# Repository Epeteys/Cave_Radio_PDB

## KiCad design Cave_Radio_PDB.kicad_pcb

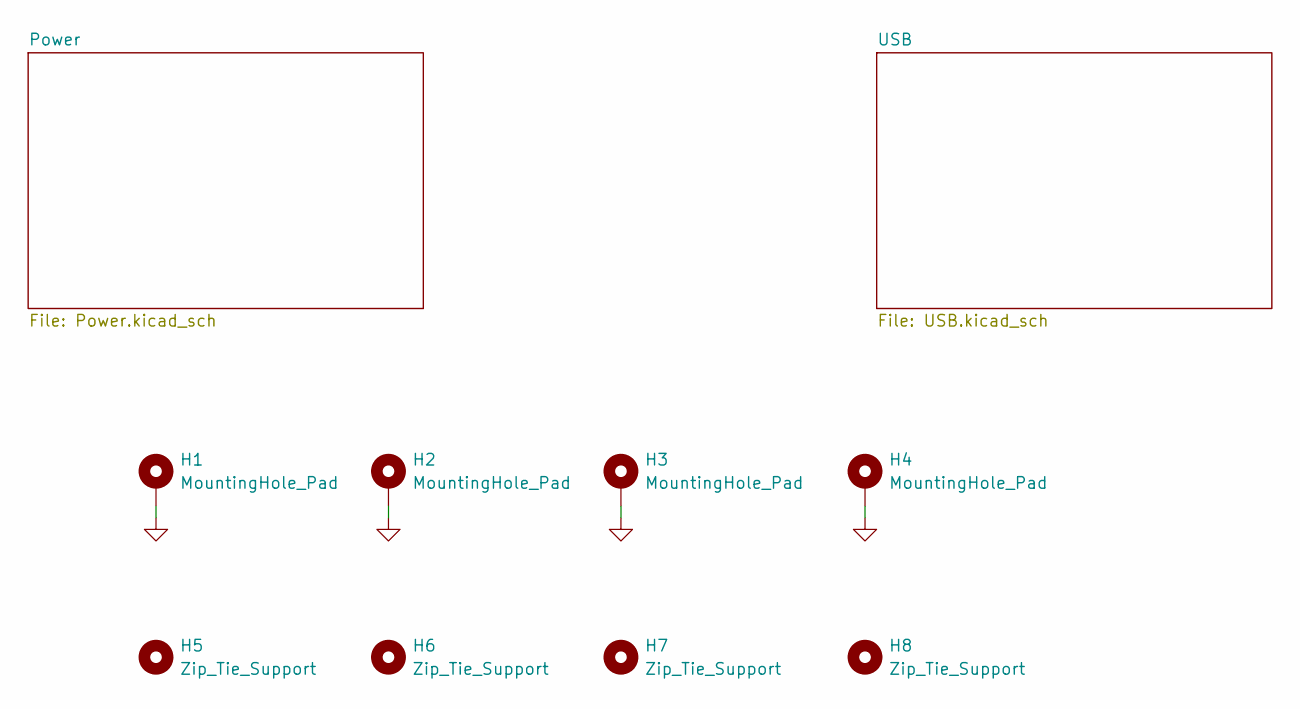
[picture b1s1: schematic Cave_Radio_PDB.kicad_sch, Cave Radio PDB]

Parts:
H1, H2, H3, H4: MountingHole_Pad; MountingHole_3.2mm_M3_DIN965_Pad_TopBottom
H5, H6, H7, H8: Zip_Tie_Support

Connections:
GND: H1.1, H2.1, H3.1, H4.1; also elsewhere on the board

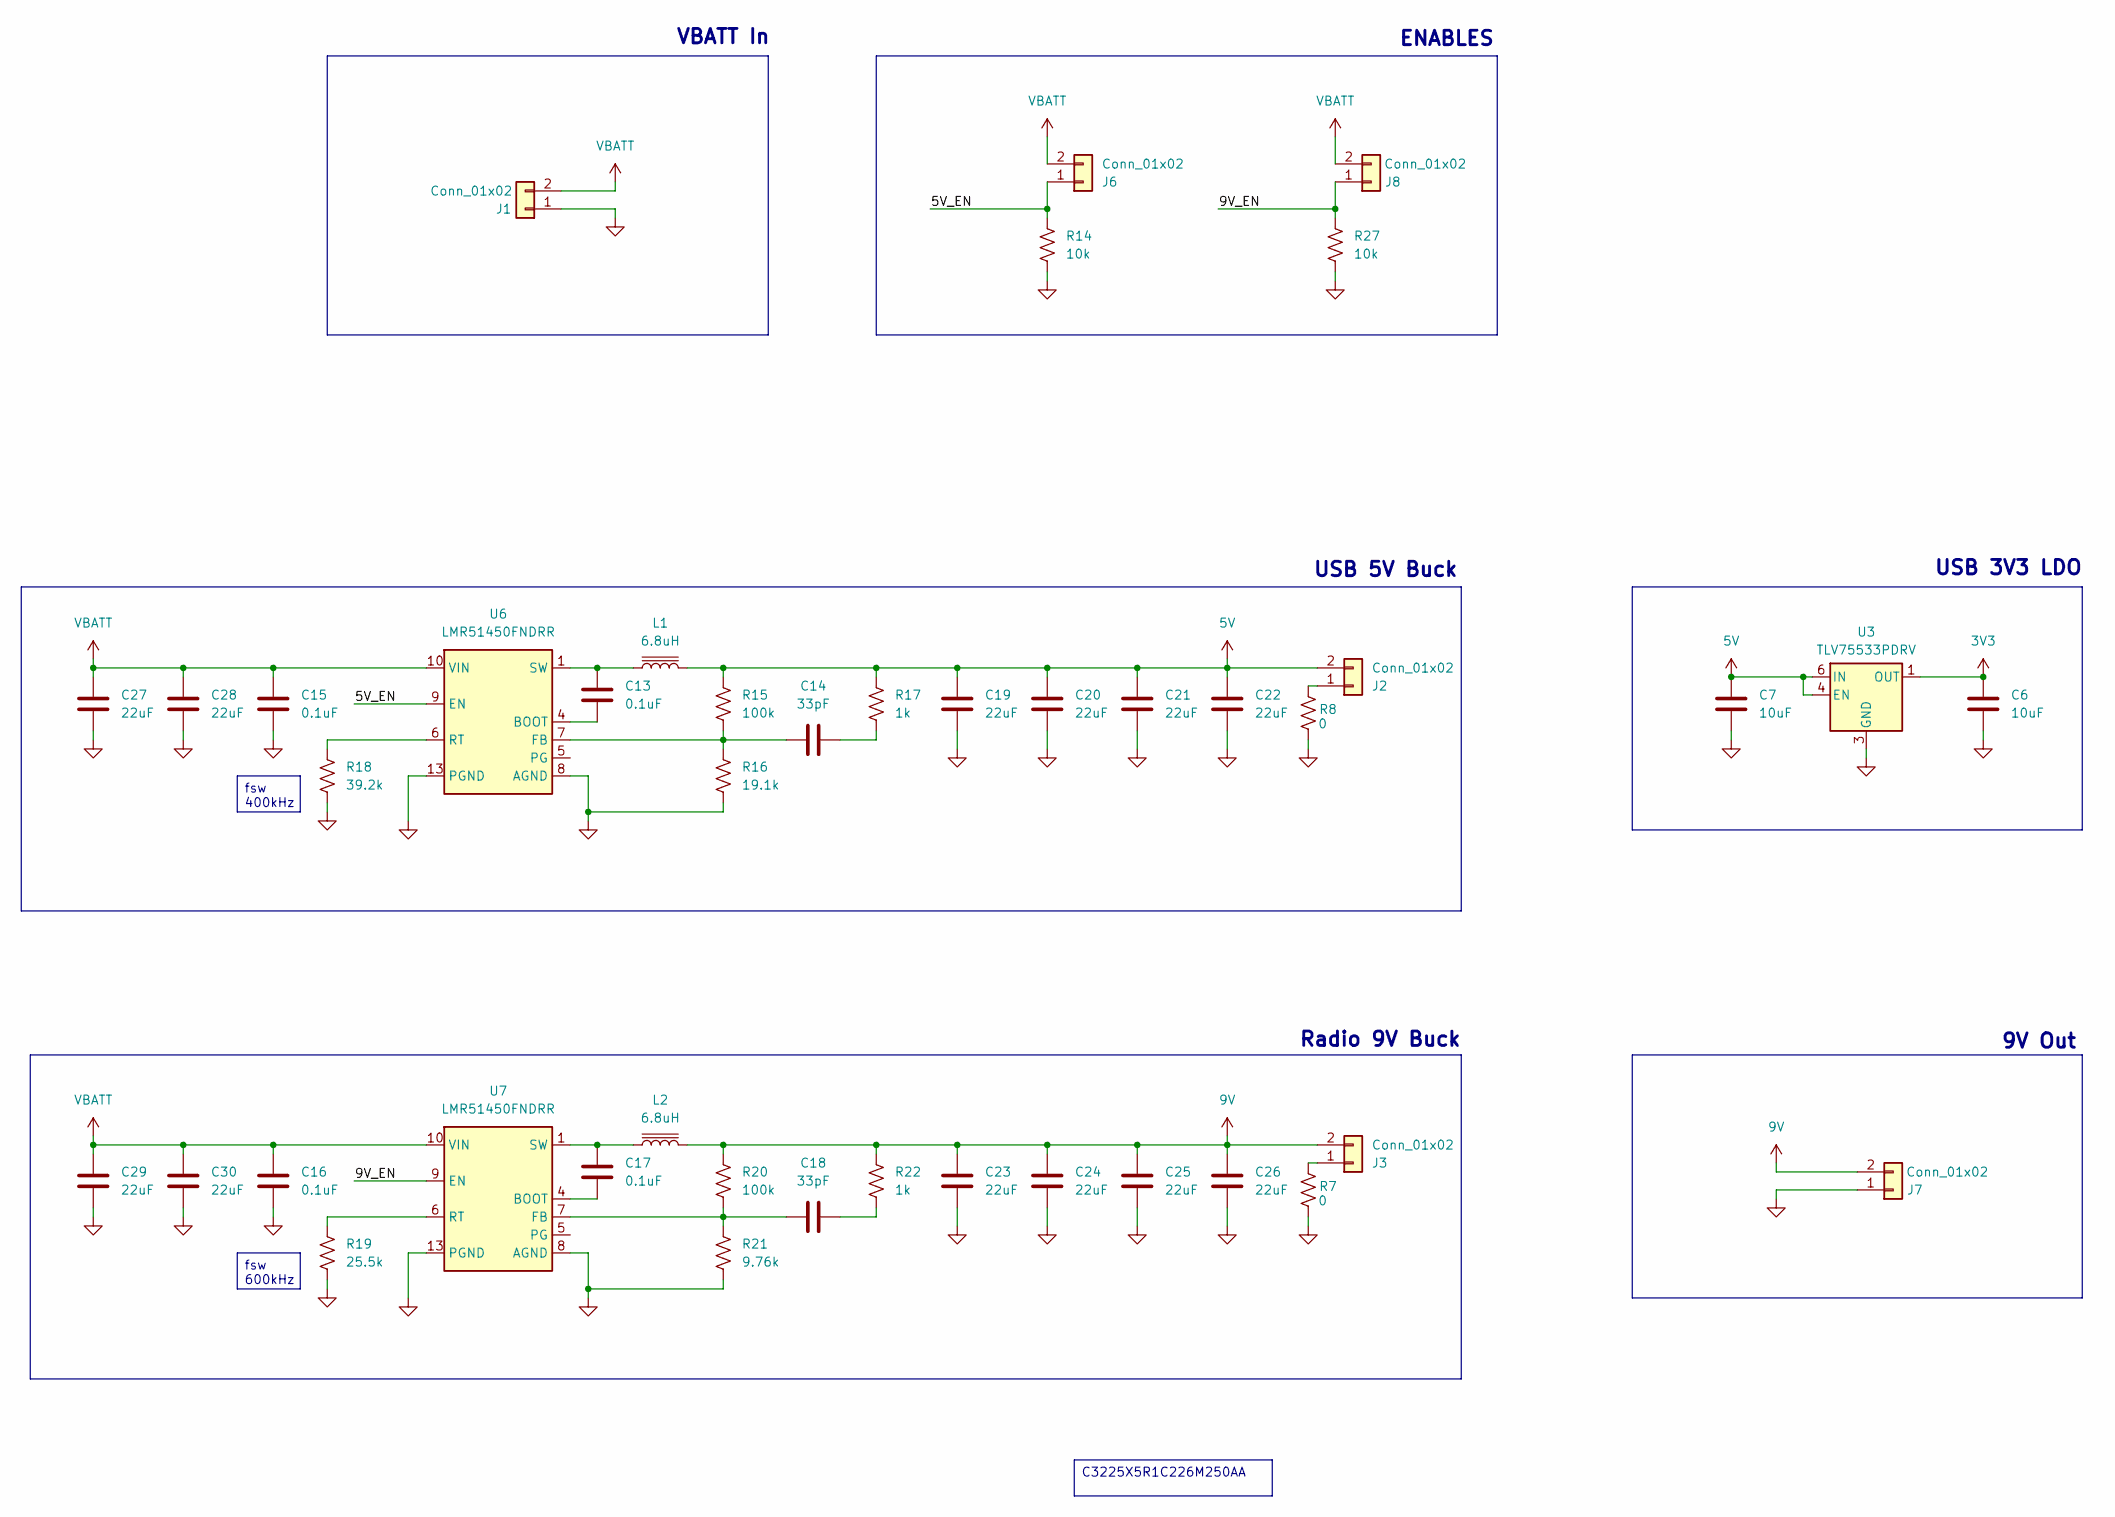
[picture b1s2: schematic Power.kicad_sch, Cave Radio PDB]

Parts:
C6, C7: 10uF; R_0603_1608Metric
C13, C15, C16, C17: 0.1uF; C_0402_1005Metric
C14, C18: 33pF; C_0402_1005Metric
C19, C20, C21, C22, C23, C24, C25, C26, C27, C28, C29, C30: 22uF; CAP_C3225X5R1C226M250AA
J1: Conn_01x02; CONN_102_PWR
J2, J3, J6, J7, J8: Conn_01x02; CONN_TSW-102-S_SAI
L1, L2: 6.8uH; IND_SPR5050_BRN-M
R7, R8: 0; R_0402_1005Metric
R14, R27: 10k; R_0402_1005Metric
R15, R20: 100k; R_0402_1005Metric
R16: 19.1k; R_0402_1005Metric
R17, R22: 1k; R_0402_1005Metric
R18: 39.2k; R_0402_1005Metric
R19: 25.5k; R_0402_1005Metric
R21: 9.76k; R_0402_1005Metric
U3: TLV75533PDRV; WSON-6-1EP_2x2mm_P0.65mm_EP1x1.6mm_ThermalVias
U6, U7: LMR51450FNDRR; WSON-12-1EP_3x3mm_P0.5mm_EP1.5x2.5mm_ThermalVias

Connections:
3V3: C6.1, U3.1 (OUT); also elsewhere on the board
5V: C7.1, C19.1, C20.1, C21.1, C22.1, J2.2, L1.2, R15.1, R17.1, U3.4 (EN), U3.6 (IN); also elsewhere on the board
9V: C23.1, C24.1, C25.1, C26.1, J3.2, J7.2, L2.2, R20.1, R22.1
/Power/5V_EN: J6.1, R14.1, U6.9 (EN)
/Power/9V_EN: J8.1, R27.1, U7.9 (EN)
GND: C6.2, C7.2, C15.2, C16.2, C19.2, C20.2, C21.2, C22.2, C23.2, C24.2, C25.2, C26.2, C27.2, C28.2, C29.2, C30.2, J1.1, J7.1, R7.1, R8.1, R14.2, R16.2, R18.2, R19.2, R21.2, R27.2, U3.3 (GND), U3.7 (GND), U6.8 (AGND), U6.13 (PGND), U7.8 (AGND), U7.13 (PGND); also elsewhere on the board
unnamed: C13.1, L1.1, U6.1 (SW), U6.2 (SW), U6.3 (SW)
unnamed: C14.2, R17.2
unnamed: C17.1, L2.1, U7.1 (SW), U7.2 (SW), U7.3 (SW)
unnamed: C18.2, R22.2
unnamed: J2.1, R8.2
unnamed: J3.1, R7.2
unnamed: C13.2, U6.4 (BOOT)
unnamed: C14.1, R15.2, R16.1, U6.7 (FB)
unnamed: R18.1, U6.6 (RT)
unnamed: C17.2, U7.4 (BOOT)
unnamed: C18.1, R20.2, R21.1, U7.7 (FB)
unnamed: R19.1, U7.6 (RT)
VBATT: C15.1, C16.1, C27.1, C28.1, C29.1, C30.1, J1.2, J6.2, J8.2, U6.10 (VIN), U6.11 (VIN), U6.12 (VIN), U7.10 (VIN), U7.11 (VIN), U7.12 (VIN)

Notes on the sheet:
USB 5V Buck
Radio 9V Buck
USB 3V3 LDO
ENABLES
VBATT In
9V Out
fsw 400kHz
fsw 600kHz
C3225X5R1C226M250AA

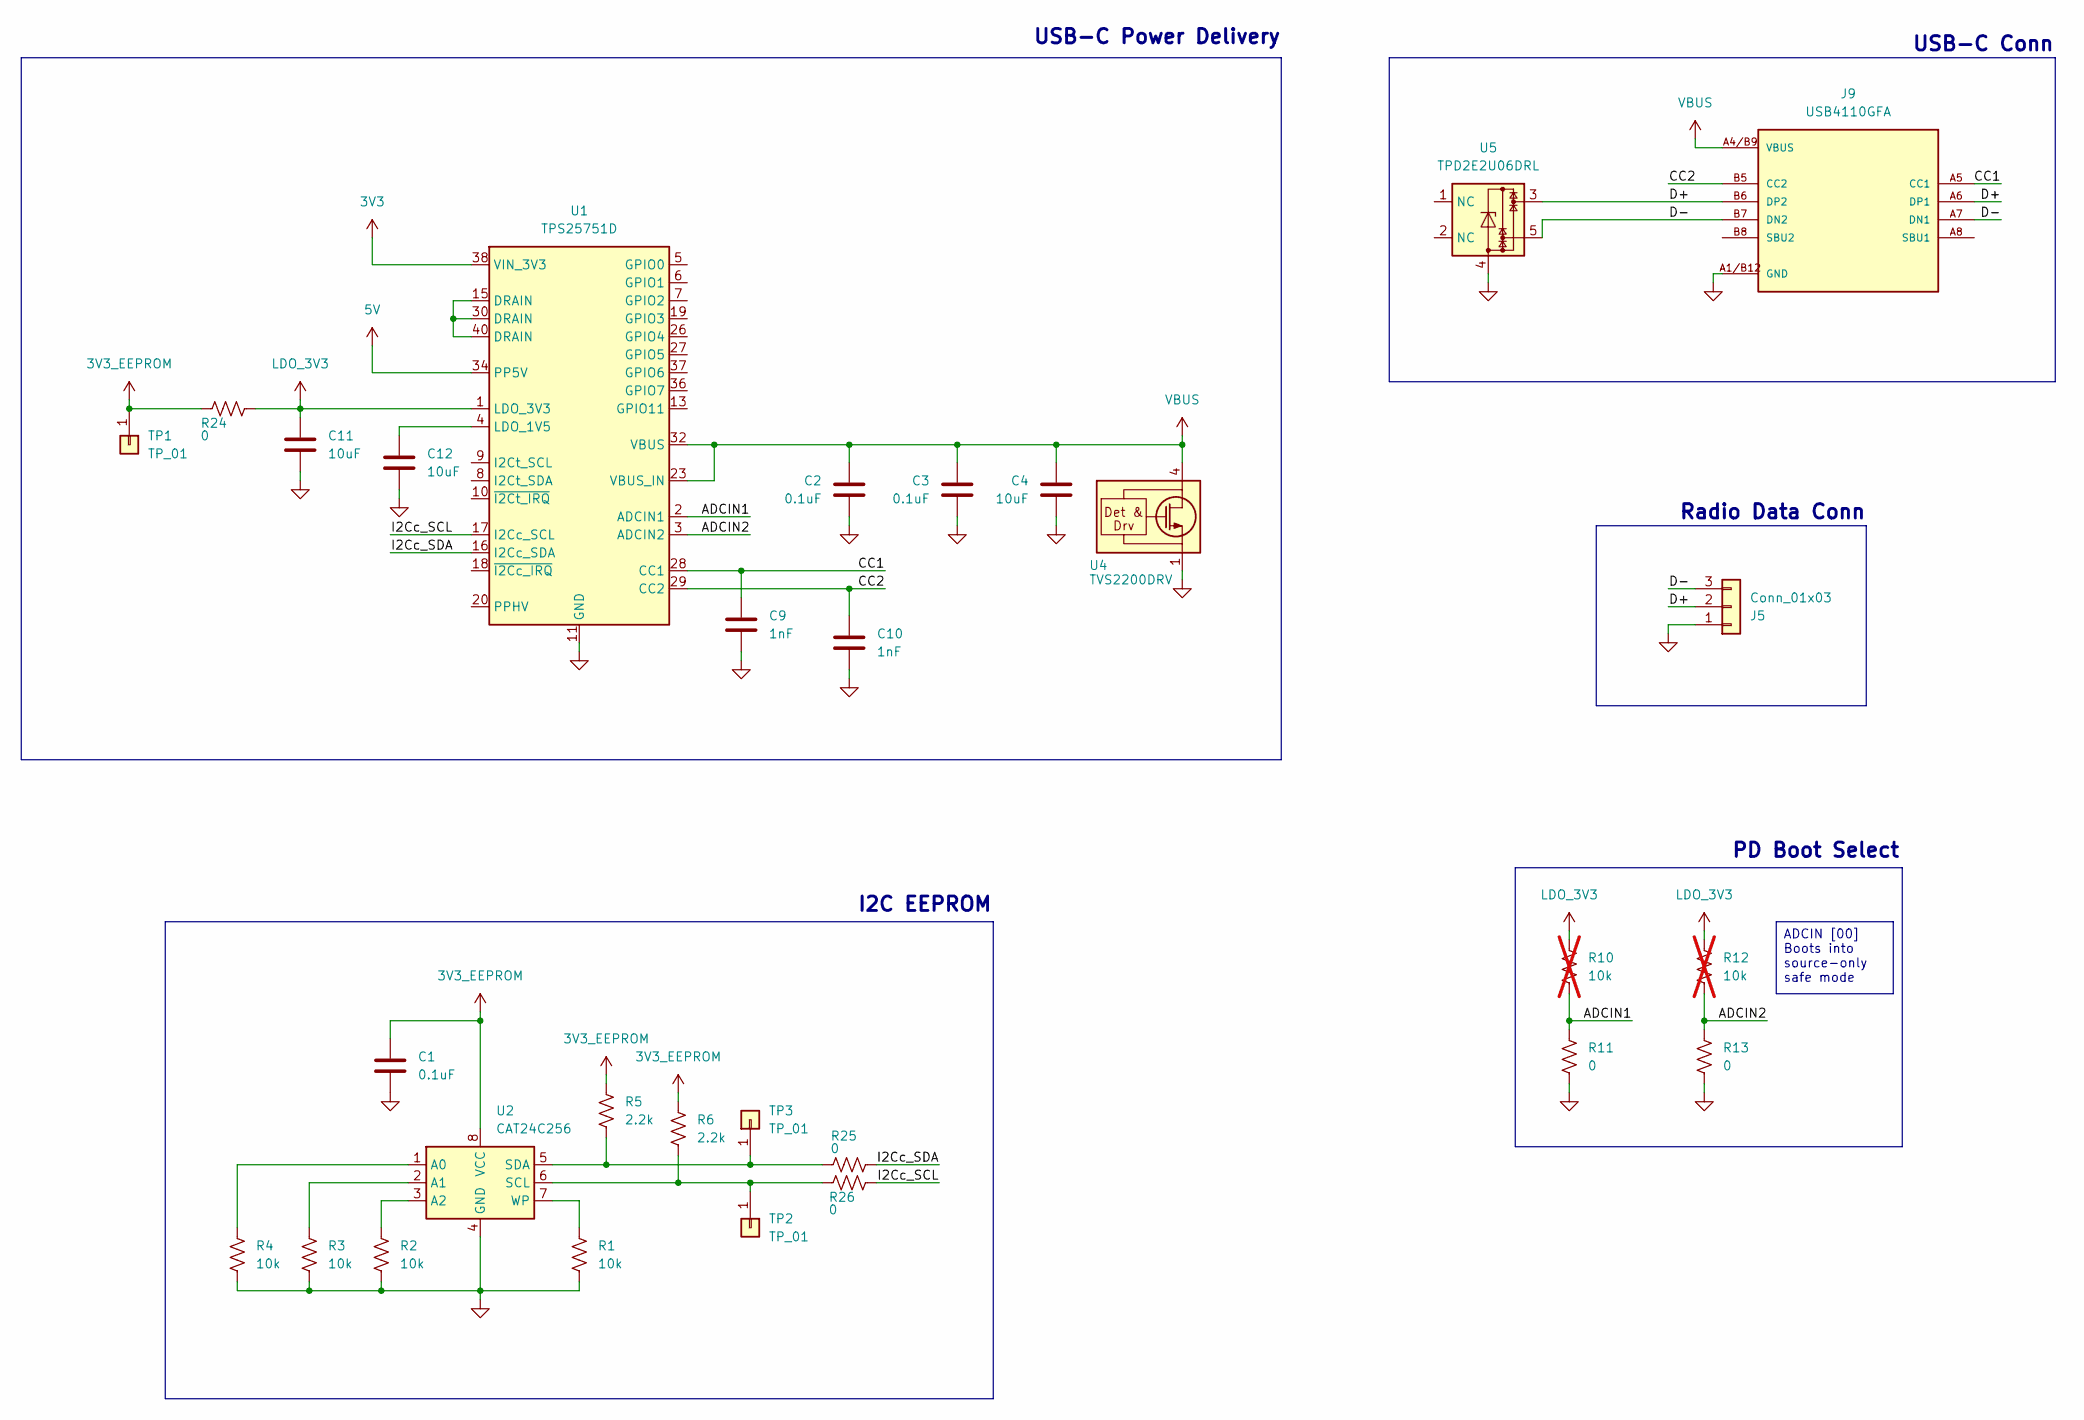
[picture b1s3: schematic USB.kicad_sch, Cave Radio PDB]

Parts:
C1, C2, C3: 0.1uF; C_0402_1005Metric
C4, C11, C12: 10uF; R_0603_1608Metric
C9, C10: 1nF; C_0402_1005Metric
J5: Conn_01x03; CONN_TSW-103-S_SAI
J9: USB4110GFA; GCT_USB4110GFA
R1, R2, R3, R4: 10k; R_0402_1005Metric
R5, R6: 2.2k; R_0402_1005Metric
R10, R12: 10k; R_0402_1005Metric; not fitted
R11, R13, R24, R25, R26: 0; R_0402_1005Metric
TP1, TP2, TP3: TP_01; CONN_TP
U1: TPS25751D; Texas_REF0038A_WQFN-38-2EP_6x4mm_P0.4
U2: CAT24C256; UDFN8_2X3_ONS
U4: TVS2200DRV; WSON-6-1EP_2x2mm_P0.65mm_EP1x1.6mm_ThermalVias
U5: TPD2E2U06DRL; SOT-553

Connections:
3V3: U1.38 (VIN_3V3); also elsewhere on the board
3V3_EEPROM: C1.1, R5.1, R6.1, R24.1, TP1.1, U2.8 (VCC)
5V: U1.34 (PP5V); also elsewhere on the board
/USB/ADCIN1: R10.2, R11.1, U1.2 (ADCIN1)
/USB/ADCIN2: R12.2, R13.1, U1.3 (ADCIN2)
/USB/CC1: C9.1, J9.A5 (CC1), U1.28 (CC1)
/USB/CC2: C10.1, J9.B5 (CC2), U1.29 (CC2)
/USB/D+: J5.2, J9.A6 (DP1), J9.B6 (DP2), U5.3
/USB/D-: J5.3, J9.A7 (DN1), J9.B7 (DN2), U5.5
/USB/I2Cc_SCL: R26.2, U1.17 (I2Cc_SCL)
/USB/I2Cc_SDA: R25.2, U1.16 (I2Cc_SDA)
GND: C1.2, C2.2, C3.2, C4.2, C9.2, C10.2, C11.2, C12.2, J5.1, J9.A1/B12 (GND), J9.B1/A12 (GND), J9.S1 (GND), J9.S2 (GND), J9.S3 (GND), J9.S4 (GND), R1.2, R2.2, R3.2, R4.2, R11.2, R13.2, U1.11 (GND), U1.12 (GND), U1.14 (GND), U1.31 (GND), U1.39 (GND), U2.4 (GND), U2.9 (PAD), U4.1 (GND), U4.2 (GND), U4.3 (GND), U4.7 (GND), U5.4; also elsewhere on the board
LDO_3V3: C11.1, R10.1, R12.1, R24.2, U1.1 (LDO_3V3)
unnamed: R6.2, R26.1, TP2.1, U2.6 (SCL)
unnamed: R5.2, R25.1, TP3.1, U2.5 (SDA)
unnamed: U1.15 (DRAIN), U1.30 (DRAIN), U1.40 (DRAIN)
unnamed: C12.1, U1.4 (LDO_1V5)
unnamed: R4.1, U2.1 (A0)
unnamed: R3.1, U2.2 (A1)
unnamed: R2.1, U2.3 (A2)
unnamed: R1.1, U2.7 (WP)
VBUS: C2.1, C3.1, C4.1, J9.A4/B9 (VBUS), J9.B4/A9 (VBUS), U1.23 (VBUS_IN), U1.32 (VBUS), U4.4 (IN), U4.5 (IN), U4.6 (IN)

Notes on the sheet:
USB-C Power Delivery
USB-C Conn
PD Boot Select
I2C EEPROM
Radio Data Conn
ADCIN [00] Boots into source-only safe mode

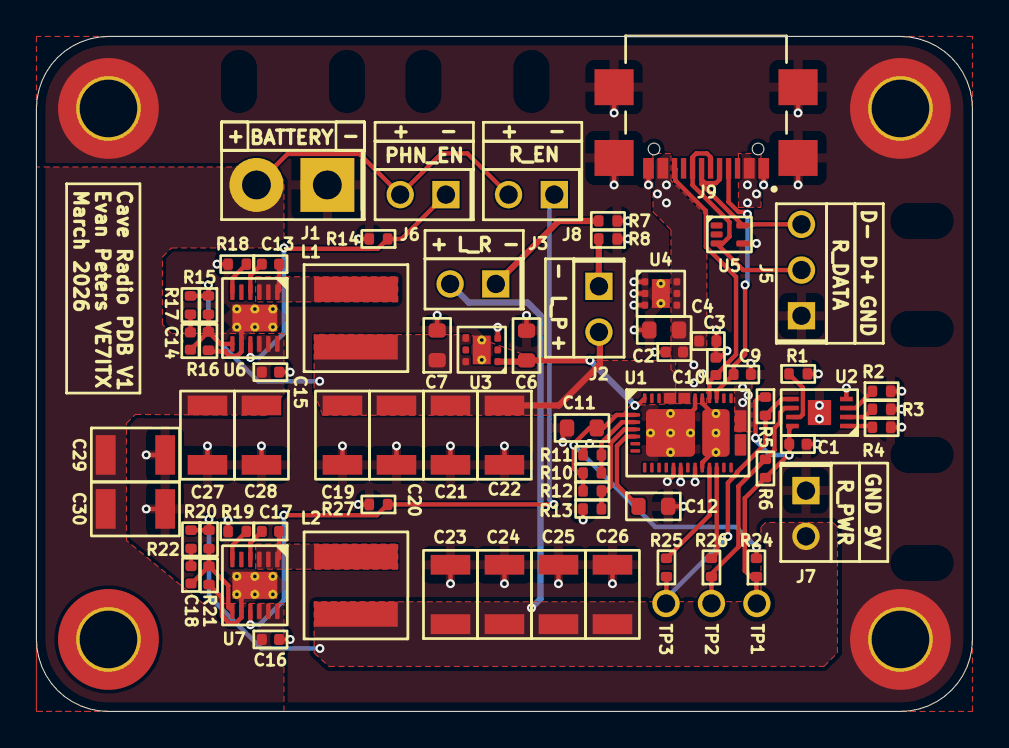
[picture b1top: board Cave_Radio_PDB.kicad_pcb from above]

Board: 2 copper layers, 52.0 x 37.5 mm, 81 parts (0 on the bottom side), 38 nets.

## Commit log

2026-03-21 add PD controller first draft
2026-03-22 add power supplies
2026-03-23 start efuse and rough layout
2026-03-24 finish efuse schematic, update connectors
2026-03-29 Update footprints
2026-04-06 start layout
2026-04-06 initial layout
2026-04-08 add via stitching
2026-04-12 remove efuse, add led connectors
2026-04-13 add bom
2026-05-02 Add Arduino I2C programming script
2026-05-03 Add Arduino code and functional firmware file
